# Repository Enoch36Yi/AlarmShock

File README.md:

# AlarmShock

As a chronic deep sleeper, I created AlarmShock to help me wake up on time when standard alarms don't work. The design uses a BMI160 accelerometer and gyroscope to measure wrist movement, an ESP32-S3 MCU, and a DRV2605L driver for a vibration motor. The goal is a wrist-worn alarm that combines motion sensing with a physical wake-up signal.

This repository contains the PCB design and its supplied fabrication exports. Firmware, Dashboard, and assembled-device test results are not included. Motion-based control and wake-up performance are not verified by the files in this repository.

*Some component body models are absent.*

## Hardware

| Part | Role in this revision |
| --- | --- |
| ESP32-S3-WROOM-1 | Controller; connected to the motion sensor and haptic driver over I2C |
| BMI160 | Accelerometer and gyroscope for wrist-motion sensing |
| DRV2605L | Haptic driver connected to the external motor header, M1 |
| MCP73831 | Battery charging circuit |
| XC6220B331MR | 3.3 V regulator |
| USB-C and USBLC6-2SC6 | USB connection and data-line ESD protection |

The motion sensor measures acceleration and angular rate; this revision has no heart-rate sensor. It has not been validated for sleep-stage detection. Component references: [Bosch BMI160 datasheet](https://www.bosch-sensortec.com/media/boschsensortec/downloads/datasheets/bst-bmi160-ds000.pdf) and [TI DRV2605L](https://www.ti.com/product/DRV2605L).

## Open the board

Use KiCad 10 and open `KiCad/Alarmshock_protofinal.kicad_pro`, then launch the PCB editor. Standard KiCad footprint libraries are required. No schematic was present in the supplied project, so this archive contains the board and its pad/net assignments rather than a complete schematic project.

To repeat the board check:

```sh
kicad-cli pcb drc --output DRC-review.rpt KiCad/Alarmshock_protofinal.kicad_pcb
```

## Current status

A fresh KiCad 10.0.5 check reports 3 warnings and 0 unconnected items. Two warnings concern silkscreen at the board edge; the third is an ESP32-S3 footprint/library mismatch. The report lists the configured ignored checks. See [DRC-current.rpt](KiCad/DRC-current.rpt); the supplied older report is preserved as `DRC-original.rpt`.

The assembly files need reconciliation before ordering: `UPLOAD_BOM_no_M1_no_U3.csv` and its CPL omit the motor and BMI160, and the board's R4 value is `e` while the assembly BOM lists 4.7 kOhm. These files are preserved as supplied. Gerbers are existing exports, not a fabrication approval. Battery charging, assembled operation, haptic output and wake-up reliability have not been verified in this review.

## Files

- `KiCad/`: editable board, project settings, component list and DRC reports.
- `gerbers/`: supplied copper, mask, paste, silkscreen, outline and drill exports.
- `previews/`: a 3D JPG exported from the unchanged board.
- `UPLOAD_BOM_no_M1_no_U3.csv` and `UPLOAD_CPL_no_M1_no_U3.csv`: supplied partial assembly files.
- `SHA256SUMS.txt`: checksums for the repository files.

The supplied folder had no development Git history to import. Original project files remain unchanged. Personal concept notes and local KiCad preferences are excluded. No license has been added.

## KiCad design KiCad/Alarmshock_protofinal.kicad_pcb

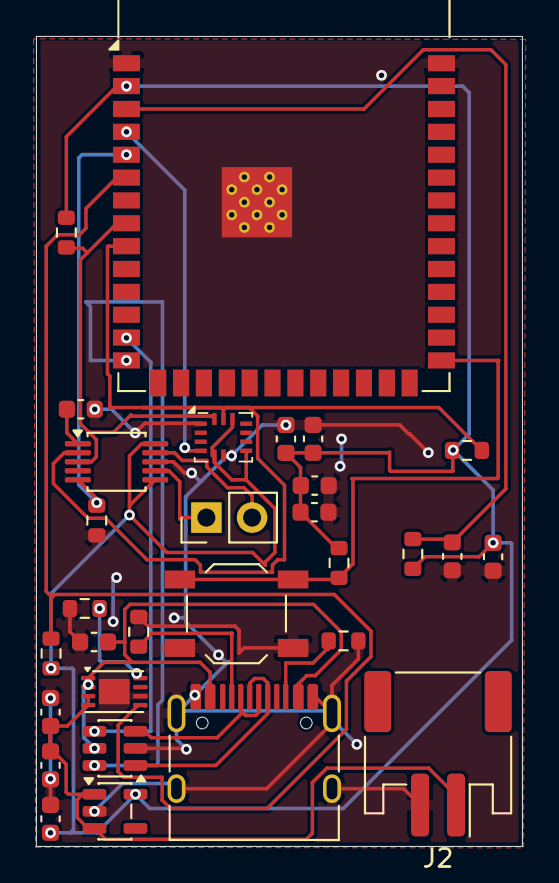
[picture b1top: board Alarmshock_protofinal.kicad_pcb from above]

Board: 2 copper layers, 27.0 x 45.0 mm, 30 parts (0 on the bottom side), 21 nets.

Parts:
C1, C2, C3, C4, C5: 10uF; C_0603_1608Metric
C6, C7: 1uF; C_0603_1608Metric
C8, C9, C10, C11: 100nF; C_0603_1608Metric
J1: USB_C_Receptacle_USB2.0_16P; USB_C_Receptacle_HRO_TYPE-C-31-M-12
J2: Conn_01x02_Socket; JST_PH_S2B-PH-SM4-TB_1x02-1MP_P2.00mm_Horizontal
M1: Motor_DC; PinHeader_1x02_P2.54mm_Vertical
R1, R2: 5.1k; R_0603_1608Metric
R3, R5: 4.7k; R_0603_1608Metric
R4: e; R_0603_1608Metric
R6, R7, R8: 10k; R_0603_1608Metric
R9: 100k; R_0603_1608Metric
SW1: BOOT; SW_SPST_TL3342
U1: ESP32-S3-WROOM-1
U2: DRV2605LDGS; TSSOP-10_3x3mm_P0.5mm
U3: BMI160; Bosch_LGA-14_3x2.5mm_P0.5mm
U4: MCP73831-2-MC; DFN-8-1EP_3x2mm_P0.5mm_EP1.7x1.4mm
U5: XC6220B331MR; SOT-23-5
U6: USBLC6-2SC6; SOT-23-6

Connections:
+3V3: C4.1, C5.1, C8.1, C9.1, C10.1, C11.1, R3.1, R4.1, R6.2, R7.1, R9.2, U1.2 (3V3), U2.6 (VDD/NC), U2.10 (VDD), U3.5 (VDDIO), U3.8 (VDD), U3.12 (CSB), U5.5 (VOUT)
/>CHG_STAT: R9.1, U1.6 (IO6), U4.5 (STAT)
/>HAPTIC_EN: R8.1, U1.5 (IO5), U2.5 (EN)
/>IMU_INT: U1.4 (IO4), U3.4 (INT1)
/>SCL: R3.2, U1.9 (IO16), U2.2 (SCL), U3.13 (SCx)
/>SDA: R4.2, U1.8 (IO15), U2.3 (SDA), U3.14 (SDx)
/>USB_DM: U1.13 (USB_D-), U6.4 (I/O2)
/>USB_DM_RAW: J1.A7 (D-), J1.B7 (D-), U6.3 (I/O2)
/>USB_DP: U1.14 (USB_D+), U6.6 (I/O1)
/>USB_DP_RAW: J1.A6 (D+), J1.B6 (D+), U6.1 (I/O1)
/VBAT: C2.1, C3.1, J2.1, U4.3 (V_{BAT}), U4.4 (V_{BAT}), U5.1 (VIN), U5.3 (CE)
/VBUS: C1.1, J1.A4 (VBUS), J1.A9 (VBUS), J1.B4 (VBUS), J1.B9 (VBUS), U4.1 (V_{DD}), U4.2 (V_{DD}), U6.5 (VBUS)
GND: C1.2, C2.2, C3.2, C4.2, C5.2, C6.2, C7.2, C8.2, C9.2, C10.2, C11.2, J1.A1 (GND), J1.A12 (GND), J1.B1 (GND), J1.B12 (GND), J1.SH (SHIELD), J2.2, R1.2, R2.2, R5.2, R8.2, SW1.2, U1.1 (GND), U1.40 (GND), U1.41 (GND), U2.8 (GND), U3.1 (SDO), U3.6 (GNDIO), U3.7 (GND), U4.6 (V_{SS}), U4.9 (EP), U5.2 (GND), U6.2 (GND)
unnamed: J1.A5 (CC1), R2.1
unnamed: J1.B5 (CC2), R1.1
unnamed: M1.1 (+), U2.7 (OUT+)
unnamed: M1.2 (-), U2.9 (OUT-)
unnamed: C7.1, R6.1, U1.3 (EN)
unnamed: R7.2, SW1.1, U1.27 (IO0)
unnamed: C6.1, U2.1 (REG)
unnamed: R5.1, U4.8 (PROG)

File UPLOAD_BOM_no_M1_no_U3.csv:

Comment,Designator,Footprint,LCSC Part #
10uF,"C1,C2,C3,C4,C5",C_0603_1608Metric,C19702
1uF,"C6,C7",C_0603_1608Metric,C15849
100nF,"C8,C9,C10,C11",C_0603_1608Metric,C14663
TYPE-C-31-M-12,J1,USB_C_Receptacle_HRO_TYPE-C-31-M-12,C165948
S2B-PH-SM4-TB,J2,JST_PH_S2B-PH-SM4-TB_1x02-1MP_P2.00mm_Horizontal,C295747
5.1k,"R1,R2",R_0603_1608Metric,C23186
4.7k,"R3,R4,R5",R_0603_1608Metric,C23162
10k,"R6,R7,R8",R_0603_1608Metric,C25804
100k,R9,R_0603_1608Metric,C25803
TL3342,SW1,SW_SPST_TL3342,C2886897
ESP32-S3-WROOM-1,U1,ESP32-S3-WROOM-1,C2913202
DRV2605LDGS,U2,TSSOP-10_3x3mm_P0.5mm,C527464
MCP73831T-2ACI/MC,U4,DFN-8-1EP_3x2mm_P0.5mm_EP1.7x1.4mm,C411870
XC6220B331MR,U5,SOT-23-5,C22466451
USBLC6-2SC6,U6,SOT-23-6,C2827654
